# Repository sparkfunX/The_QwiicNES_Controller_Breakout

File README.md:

# The_QwiicNES_Controller_Breakout
Qwiic to Nintendo Entertainment System Controller Board

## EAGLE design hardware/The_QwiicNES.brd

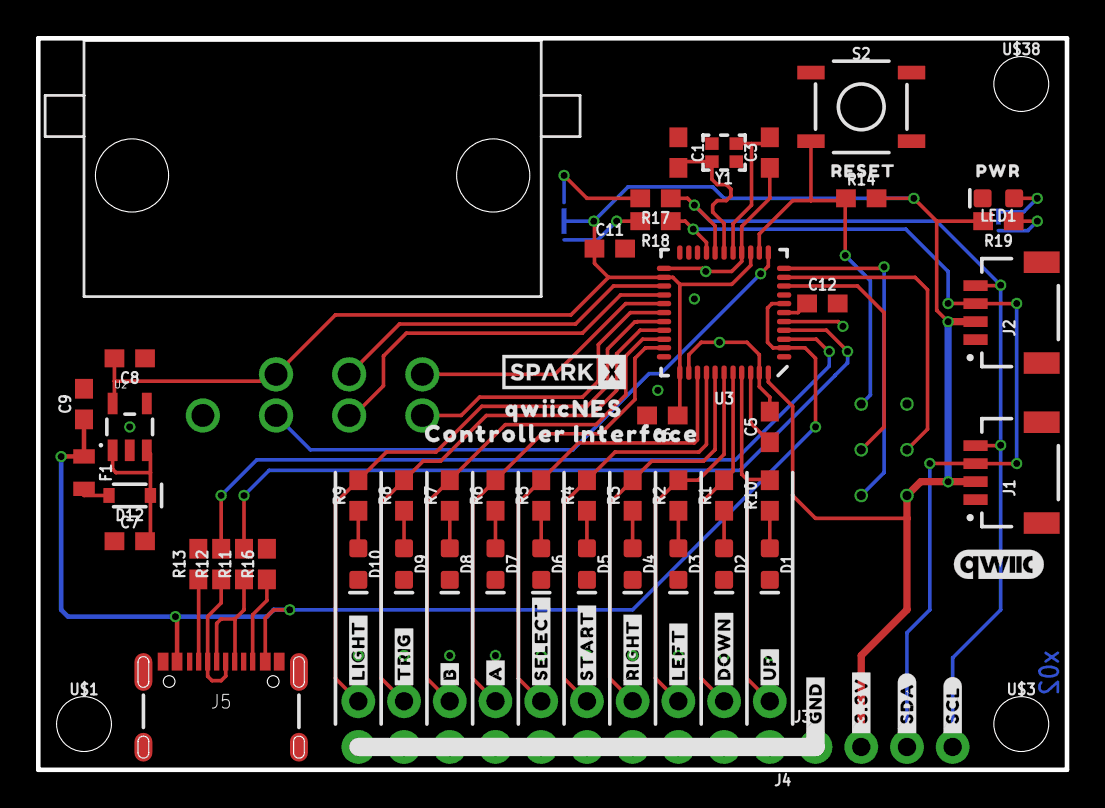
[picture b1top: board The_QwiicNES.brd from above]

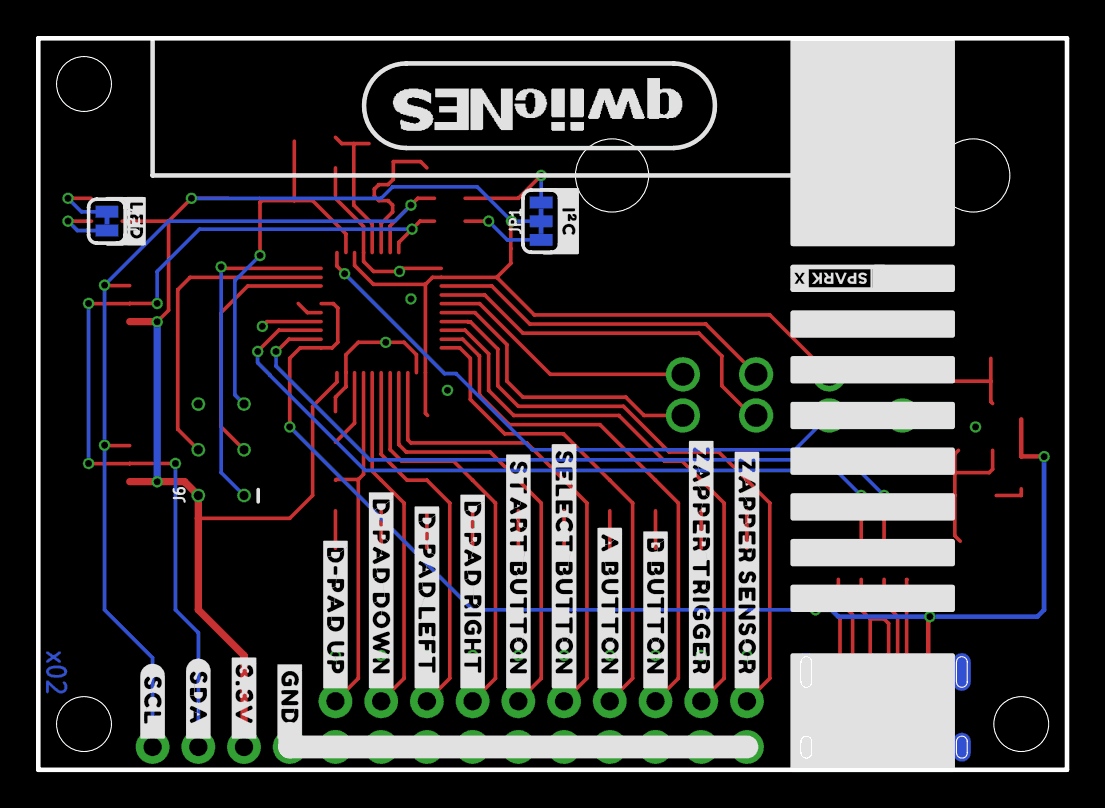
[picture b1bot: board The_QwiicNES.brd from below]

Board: 2 copper layers, 57.1 x 40.6 mm, 95 parts (21 on the bottom side), 50 nets.

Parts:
C1, C3: 22pF; 0603
C5, C6: 0.1uF; 0603
C7, C8: 10uF; 0603
C9, C11, C12: 1.0uF; 0603
D1, D2, D3, D4, D5, D6, D7, D8, D9, D10: GREEN; LED-0603
D12: 3A/10V/280mV; SOD-323
F1: 6V 0.5A; 0805
FRAME1: FRAME-LETTER; CREATIVE_COMMONS
J1, J2: QWIIC_RIGHT_ANGLE; JST04_1MM_RA
J3: 1X04_NO_SILK
J4: 2X10_NOSILK
J5: USB-C-16P-5
J6: AVR_SPI_PROG_3X2TESTPOINTS; 2X3_TEST_POINTS
J7: NES_CONTROLLER_PORT; NES_CONTROLLER_PORT_7PIN_90
JP1: JUMPER-SMT_3_2-NC_TRACE_SILK; SMT-JUMPER_3_2-NC_TRACE_SILK
JP2: JUMPER-SMT_2_NC_TRACE_SILK; SMT-JUMPER_2_NC_TRACE_SILK
LED1: RED; LED-0603
R1, R2, R3, R4, R5, R6, R7, R8, R9, R10, R19: 1k; 0603
R11, R12: 22; 0603
R13, R16: 5.1k; 0603
R14: 10k; 0603
R17, R18: 2.2k; 0603
S2: MOMENTARY-SWITCH-SPST-SMD-5.2MM-TALL; TACTILE_SWITCH_SMD_5.2MM
U2: 3.3V; SOT23-5
U3: 32U4; QFN-44-NOPAD_1:1-LESS_PASTE
U$1, U$3, U$38: STAND-OFF-TIGHT
U$2: SPARKX-SMALL
U$4: #LIGHT#0
U$5: #TRIG#0
U$6: #B#0
U$7: #A#0
U$8: #SELECT#0
U$9: #START#0
U$10: #RIGHT#0
U$11: #LEFT#0
U$12: #DOWN#0
U$13: #UP#0
U$14: #_GND#0
U$15: #_SDA#0
U$16: #_SCL#0
U$17: #_3#3V#0
U$18: PWR0
U$19: RESET0
U$20: SPARKX-TINY
U$21: #ZAPPER_SENSOR_#0
U$22: #ZAPPER_TRIGGER_#0
U$23: #B_BUTTON_#0
U$24: #A_BUTTON_#0
U$25: #SELECT_BUTTON_#0
U$26: #START_BUTTON_#0
U$27: #D#PAD_RIGHT_#0
U$28: #D#PAD_LEFT_#0
U$29: #D#PAD_DOWN_#0
U$30: #D#PAD_UP_#0
U$31: #GND_#0
U$32: #SDA_#0
U$33: #SCL_#0
U$34: #3#3V_#0
U$35: #I�C#0
U$36: #LED#0
U$37: QWIICNESS#PNG
U$39: QWIICNES0
U$40: CONTROLLER_INTERFACE0
U$41: QWIIC_5MM
Y1: 16MHz; CRYSTAL-SMD-2.0X1.6MM

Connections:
3.3V: C6.1, C8.2, C11.1, J1.2, J2.2, J3.2, J6.2, J7.7, JP1.2, R14.2, R19.2, U2.5, U3.14, U3.24, U3.34, U3.44
5V: C7.2, D12.C, U2.1, U2.3
!RESET: J6.5, R14.1, S2.3, U3.13
AREF: C5.1, U3.42
A_LED: J4.13, R6.2, U3.32
B_LED: J4.15, R7.2, U3.31
D-_HV: J5.A7, J5.B7, R12.1
DI: J6.1, U3.11
DN_LED: J4.3, R1.2, U3.40
DO: J6.4, U3.10
DP_HV: J5.A6, J5.B6, R11.1
D_N: R12.2, U3.3
D_P: R11.2, U3.4
GND: C1.1, C3.1, C5.2, C6.2, C7.1, C8.1, C9.2, C11.2, C12.2, D1.C, D2.C, D3.C, D4.C, D5.C, D6.C, D7.C, D8.C, D9.C, D10.C, J1.1, J2.1, J3.1, J4.2, J4.4, J4.6, J4.8, J4.10, J4.12, J4.14, J4.16, J4.18, J4.20, J5.GND, J5.GND2, J6.6, J7.1, LED1.C, R13.2, R16.2, S2.1, U2.2, U3.5, U3.15, U3.23, U3.33, U3.35, U3.43
LF_LED: J4.5, R2.2, U3.39
unnamed: C3.2, U3.16, Y1.1
unnamed: C1.2, U3.17, Y1.3
unnamed: D1.A, R10.1
unnamed: D2.A, R1.1
unnamed: D3.A, R2.1
unnamed: D4.A, R3.1
unnamed: D5.A, R4.1
unnamed: D6.A, R5.1
unnamed: J5.A5, R13.1
unnamed: J5.B5, R16.1
unnamed: D8.A, R7.1
unnamed: D7.A, R6.1
unnamed: JP2.2, R19.1
unnamed: JP2.1, LED1.A
unnamed: JP1.3, R17.2
unnamed: JP1.1, R18.2
unnamed: D10.A, R9.1
unnamed: D9.A, R8.1
NES_CLK: J7.2, U3.12
NES_DATA: J7.4, U3.28
NES_LATCH: J7.3, U3.26
RT_LED: J4.7, R3.2, U3.38
SCK: J6.3, U3.9
SCL: J1.4, J2.4, J3.4, R17.1, U3.18
SDA: J1.3, J2.3, J3.3, R18.1, U3.19
SELECT_LED: J4.11, R5.2, U3.36
START_LED: J4.9, R4.2, U3.37
UCAP: C12.1, U3.6
UP_LED: J4.1, R10.2, U3.41
USB_RAW: D12.A, F1.2
V_USB: C9.1, F1.1, J5.VBUS1, J5.VBUS2, U3.2, U3.7
ZAP_LIGHT: J7.6, U3.25
ZAP_LIGHT_LED: J4.19, R9.2, U3.29
ZAP_TRIGGER: J7.5, U3.27
ZAP_TRIG_LED: J4.17, R8.2, U3.30

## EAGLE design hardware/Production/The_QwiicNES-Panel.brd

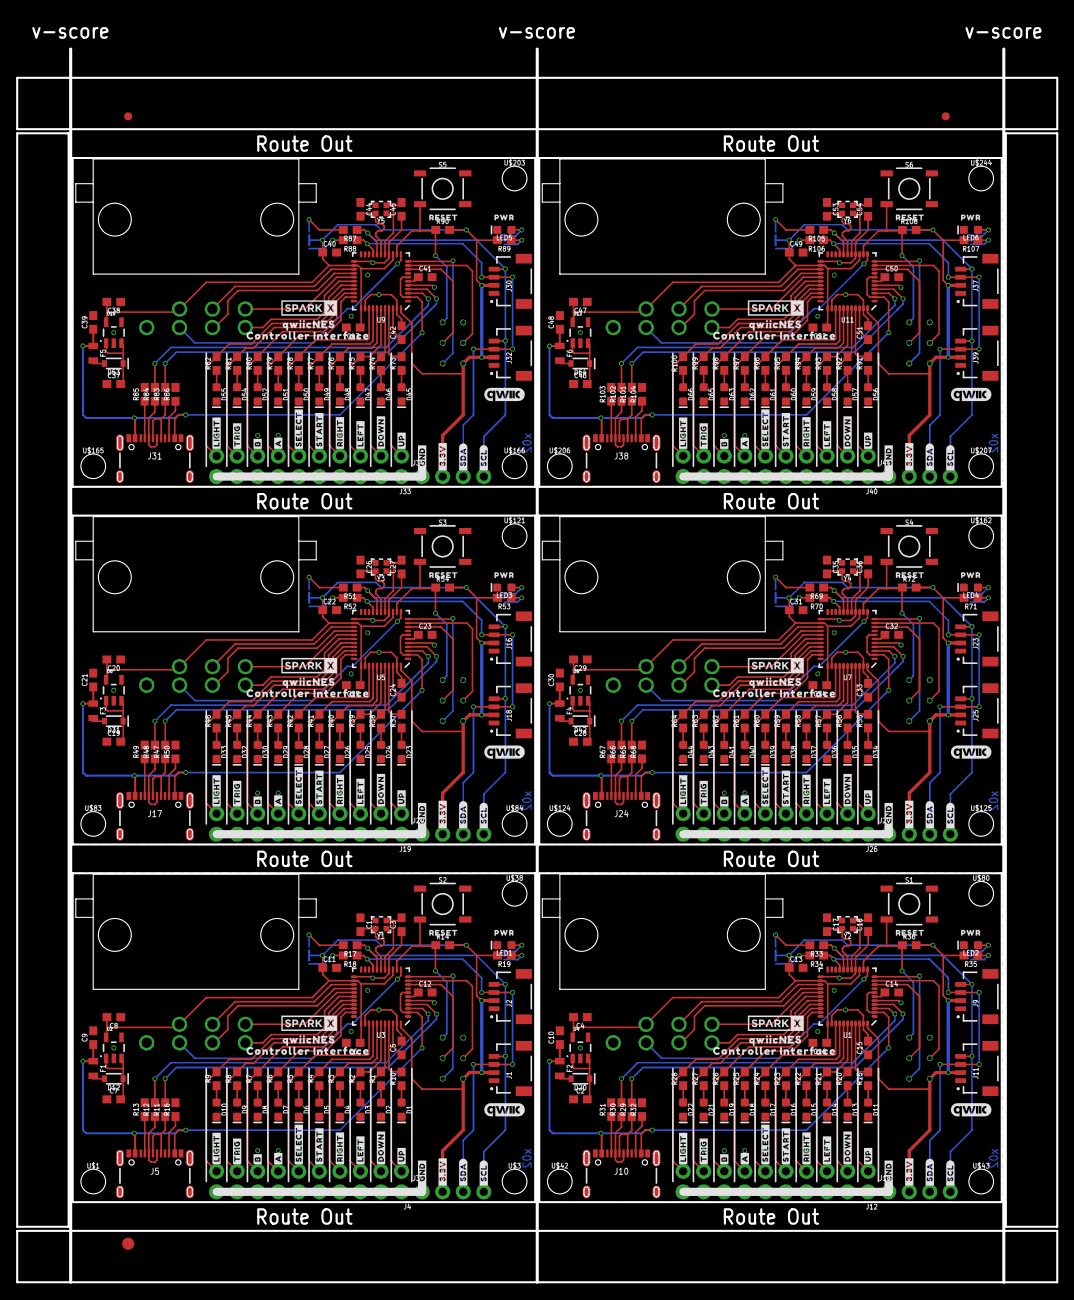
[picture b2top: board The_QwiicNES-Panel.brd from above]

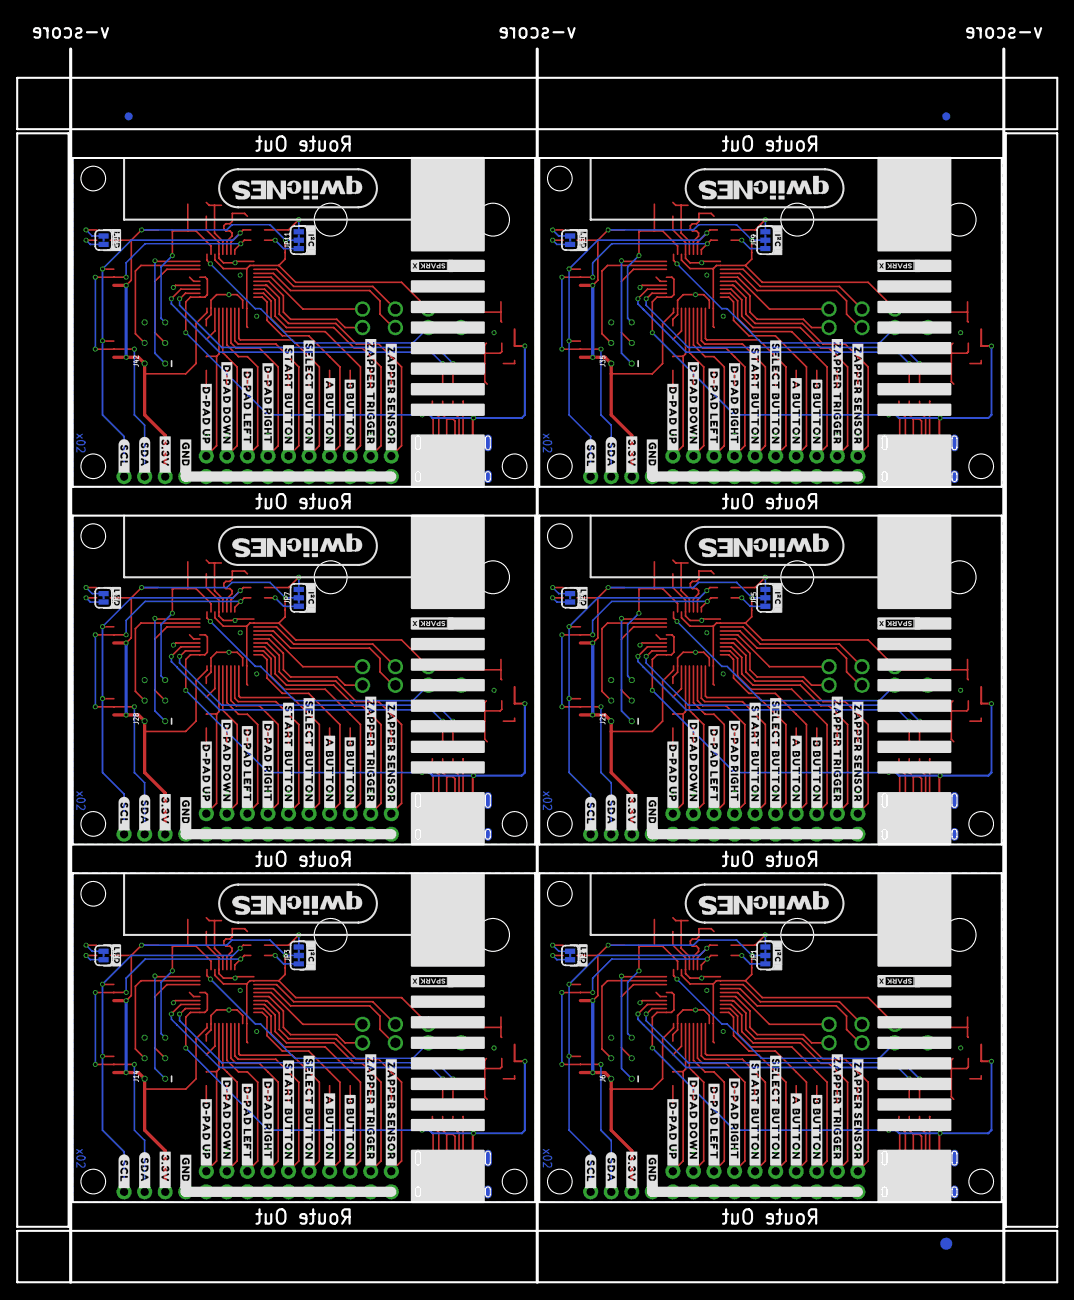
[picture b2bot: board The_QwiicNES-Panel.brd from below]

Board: 2 copper layers, 128.4 x 156.3 mm, 570 parts (129 on the bottom side), 300 nets.

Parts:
C1, C3, C17, C18, C26, C27, C35, C36, C44, C45, C53, C54: 22pF; 0603
C2, C4, C7, C8, C19, C20, C28, C29, C37, C38, C46, C47: 10uF; 0603
C5, C6, C15, C16, C24, C25, C33, C34, C42, C43, C51, C52: 0.1uF; 0603
C9, C10, C11, C12, C13, C14, C21, C22, C23, C30, C31, C32, C39, C40, C41, C48, C49, C50: 1.0uF; 0603
D1, D2, D3, D4, D5, D6, D7, D8, D9, D10, D11, D13, D14, D15, D16, D17, D18, D19, D21, D22, D23, D24, D25, D26, D27, D28, D29, D30, D32, D33, D34, D35, D36, D37, D38, D39, D40, D41, D43, D44, D45, D46, D47, D48, D49, D50, D51, D52, D54, D55, D56, D57, D58, D59, D60, D61, D62, D63, D65, D66: GREEN; LED-0603
D12, D20, D31, D42, D53, D64: 3A/10V/280mV; SOD-323
E$1, E$2, E$3, E$4: FIDUCIAL-1X2
E$5, E$6: FIDUCIAL-1.5X3
F1, F2, F3, F4, F5, F6: 6V 0.5A; 0805
J1, J2, J9, J11, J16, J18, J23, J25, J30, J32, J37, J39: QWIIC_RIGHT_ANGLE; JST04_1MM_RA
J3, J13, J20, J27, J34, J41: 1X04_NO_SILK
J4, J12, J19, J26, J33, J40: 2X10_NOSILK
J5, J10, J17, J24, J31, J38: USB-C-16P-5
J6, J14, J21, J28, J35, J42: AVR_SPI_PROG_3X2TESTPOINTS; 2X3_TEST_POINTS
J7, J8, J15, J22, J29, J36: NES_CONTROLLER_PORT; NES_CONTROLLER_PORT_7PIN_90
JP1, JP3, JP5, JP7, JP9, JP11: JUMPER-SMT_3_2-NC_TRACE_SILK; SMT-JUMPER_3_2-NC_TRACE_SILK
JP2, JP4, JP6, JP8, JP10, JP12: JUMPER-SMT_2_NC_TRACE_SILK; SMT-JUMPER_2_NC_TRACE_SILK
LED1, LED2, LED3, LED4, LED5, LED6: RED; LED-0603
R1, R2, R3, R4, R5, R6, R7, R8, R9, R10, R15, R19, R20, R21, R22, R23, R24, R25, R26, R27, R28, R35, R37, R38, R39, R40, R41, R42, R43, R44, R45, R46, R53, R55, R56, R57, R58, R59, R60, R61, R62, R63, R64, R71, R73, R74, R75, R76, R77, R78, R79, R80, R81, R82, R89, R91, R92, R93, R94, R95, R96, R97, R98, R99, R100, R107: 1k; 0603
R11, R12, R29, R30, R47, R48, R65, R66, R83, R84, R101, R102: 22; 0603
R13, R16, R31, R32, R49, R50, R67, R68, R85, R86, R103, R104: 5.1k; 0603
R14, R36, R54, R72, R90, R108: 10k; 0603
R17, R18, R33, R34, R51, R52, R69, R70, R87, R88, R105, R106: 2.2k; 0603
S1, S2, S3, S4, S5, S6: MOMENTARY-SWITCH-SPST-SMD-5.2MM-TALL; TACTILE_SWITCH_SMD_5.2MM
U1, U3, U5, U7, U9, U11: 32U4; QFN-44-NOPAD_1:1-LESS_PASTE
U2, U4, U6, U8, U10, U12: 3.3V; SOT23-5
U$1, U$3, U$38, U$42, U$43, U$80, U$83, U$84, U$121, U$124, U$125, U$162, U$165, U$166, U$203, U$206, U$207, U$244: STAND-OFF-TIGHT
U$2, U$79, U$120, U$161, U$202, U$243: SPARKX-SMALL
U$4, U$44, U$85, U$126, U$167, U$208: #LIGHT#0
U$5, U$45, U$86, U$127, U$168, U$209: #TRIG#0
U$6, U$46, U$87, U$128, U$169, U$210: #B#0
U$7, U$47, U$88, U$129, U$170, U$211: #A#0
U$8, U$48, U$89, U$130, U$171, U$212: #SELECT#0
U$9, U$49, U$90, U$131, U$172, U$213: #START#0
U$10, U$50, U$91, U$132, U$173, U$214: #RIGHT#0
U$11, U$51, U$92, U$133, U$174, U$215: #LEFT#0
U$12, U$52, U$93, U$134, U$175, U$216: #DOWN#0
U$13, U$53, U$94, U$135, U$176, U$217: #UP#0
U$14, U$59, U$100, U$141, U$182, U$223: #_GND#0
U$15, U$54, U$95, U$136, U$177, U$218: #_SDA#0
U$16, U$55, U$96, U$137, U$178, U$219: #_SCL#0
U$17, U$56, U$97, U$138, U$179, U$220: #_3#3V#0
U$18, U$57, U$98, U$139, U$180, U$221: PWR0
U$19, U$58, U$99, U$140, U$181, U$222: RESET0
U$20, U$75, U$116, U$157, U$198, U$239: SPARKX-TINY
U$21, U$60, U$101, U$142, U$183, U$224: #ZAPPER_SENSOR_#0
U$22, U$61, U$102, U$143, U$184, U$225: #ZAPPER_TRIGGER_#0
U$23, U$62, U$103, U$144, U$185, U$226: #B_BUTTON_#0
U$24, U$63, U$104, U$145, U$186, U$227: #A_BUTTON_#0
U$25, U$64, U$105, U$146, U$187, U$228: #SELECT_BUTTON_#0
U$26, U$65, U$106, U$147, U$188, U$229: #START_BUTTON_#0
U$27, U$66, U$107, U$148, U$189, U$230: #D#PAD_RIGHT_#0
U$28, U$67, U$108, U$149, U$190, U$231: #D#PAD_LEFT_#0
U$29, U$68, U$109, U$150, U$191, U$232: #D#PAD_DOWN_#0
U$30, U$69, U$110, U$151, U$192, U$233: #D#PAD_UP_#0
U$31, U$70, U$111, U$152, U$193, U$234: #GND_#0
U$32, U$71, U$112, U$153, U$194, U$235: #SDA_#0
U$33, U$72, U$113, U$154, U$195, U$236: #SCL_#0
U$34, U$73, U$114, U$155, U$196, U$237: #3#3V_#0
U$35, U$74, U$115, U$156, U$197, U$238: #I�C#0
U$36, U$82, U$123, U$164, U$205, U$246: #LED#0
U$37, U$76, U$117, U$158, U$199, U$240: QWIICNESS#PNG
U$39, U$77, U$118, U$159, U$200, U$241: QWIICNES0
U$40, U$78, U$119, U$160, U$201, U$242: CONTROLLER_INTERFACE0
U$41, U$81, U$122, U$163, U$204, U$245: QWIIC_5MM
Y1, Y2, Y3, Y4, Y5, Y6: 16MHz; CRYSTAL-SMD-2.0X1.6MM

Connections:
3.3V: C6.1, C8.2, C11.1, J1.2, J2.2, J3.2, J6.2, J7.7, JP1.2, R14.2, R19.2, U2.5, U3.14, U3.24, U3.34, U3.44
3.3V1: C4.2, C13.1, C16.1, J8.7, J9.2, J11.2, J13.2, J14.2, JP3.2, R35.2, R36.2, U1.14, U1.24, U1.34, U1.44, U4.5
3.3V2: C20.2, C22.1, C25.1, J15.7, J16.2, J18.2, J20.2, J21.2, JP5.2, R53.2, R54.2, U5.14, U5.24, U5.34, U5.44, U6.5
3.3V3: C29.2, C31.1, C34.1, J22.7, J23.2, J25.2, J27.2, J28.2, JP7.2, R71.2, R72.2, U7.14, U7.24, U7.34, U7.44, U8.5
3.3V4: C38.2, C40.1, C43.1, J29.7, J30.2, J32.2, J34.2, J35.2, JP9.2, R89.2, R90.2, U9.14, U9.24, U9.34, U9.44, U10.5
3.3V5: C47.2, C49.1, C52.1, J36.7, J37.2, J39.2, J41.2, J42.2, JP11.2, R107.2, R108.2, U11.14, U11.24, U11.34, U11.44, U12.5
5V: C7.2, D12.C, U2.1, U2.3
5V1: C2.2, D20.C, U4.1, U4.3
5V2: C19.2, D31.C, U6.1, U6.3
5V3: C28.2, D42.C, U8.1, U8.3
5V4: C37.2, D53.C, U10.1, U10.3
5V5: C46.2, D64.C, U12.1, U12.3
!RESET: J6.5, R14.1, S2.3, U3.13
!RESET1: J14.5, R36.1, S1.3, U1.13
!RESET2: J21.5, R54.1, S3.3, U5.13
!RESET3: J28.5, R72.1, S4.3, U7.13
!RESET4: J35.5, R90.1, S5.3, U9.13
!RESET5: J42.5, R108.1, S6.3, U11.13
AREF: C5.1, U3.42
AREF1: C15.1, U1.42
AREF2: C24.1, U5.42
AREF3: C33.1, U7.42
AREF4: C42.1, U9.42
AREF5: C51.1, U11.42
A_LED: J4.13, R6.2, U3.32
A_LED1: J12.13, R25.2, U1.32
A_LED2: J19.13, R43.2, U5.32
A_LED3: J26.13, R61.2, U7.32
A_LED4: J33.13, R79.2, U9.32
A_LED5: J40.13, R97.2, U11.32
B_LED: J4.15, R7.2, U3.31
B_LED1: J12.15, R26.2, U1.31
B_LED2: J19.15, R44.2, U5.31
B_LED3: J26.15, R62.2, U7.31
B_LED4: J33.15, R80.2, U9.31
B_LED5: J40.15, R98.2, U11.31
D-_HV: J5.A7, J5.B7, R12.1
D-_HV1: J10.A7, J10.B7, R30.1
D-_HV2: J17.A7, J17.B7, R48.1
D-_HV3: J24.A7, J24.B7, R66.1
D-_HV4: J31.A7, J31.B7, R84.1
D-_HV5: J38.A7, J38.B7, R102.1
DI: J6.1, U3.11
DI1: J14.1, U1.11
DI2: J21.1, U5.11
DI3: J28.1, U7.11
DI4: J35.1, U9.11
DI5: J42.1, U11.11
DN_LED: J4.3, R1.2, U3.40
DN_LED1: J12.3, R20.2, U1.40
DN_LED2: J19.3, R38.2, U5.40
DN_LED3: J26.3, R56.2, U7.40
DN_LED4: J33.3, R74.2, U9.40
DN_LED5: J40.3, R92.2, U11.40
DO: J6.4, U3.10
DO1: J14.4, U1.10
DO2: J21.4, U5.10
DO3: J28.4, U7.10
DO4: J35.4, U9.10
DO5: J42.4, U11.10
DP_HV: J5.A6, J5.B6, R11.1
DP_HV1: J10.A6, J10.B6, R29.1
DP_HV2: J17.A6, J17.B6, R47.1
DP_HV3: J24.A6, J24.B6, R65.1
DP_HV4: J31.A6, J31.B6, R83.1
DP_HV5: J38.A6, J38.B6, R101.1
D_N: R12.2, U3.3
D_N1: R30.2, U1.3
D_N2: R48.2, U5.3
D_N3: R66.2, U7.3
D_N4: R84.2, U9.3
D_N5: R102.2, U11.3
D_P: R11.2, U3.4
D_P1: R29.2, U1.4
D_P2: R47.2, U5.4
D_P3: R65.2, U7.4
D_P4: R83.2, U9.4
D_P5: R101.2, U11.4
GND: C1.1, C3.1, C5.2, C6.2, C7.1, C8.1, C9.2, C11.2, C12.2, D1.C, D2.C, D3.C, D4.C, D5.C, D6.C, D7.C, D8.C, D9.C, D10.C, J1.1, J2.1, J3.1, J4.2, J4.4, J4.6, J4.8, J4.10, J4.12, J4.14, J4.16, J4.18, J4.20, J5.GND, J5.GND2, J6.6, J7.1, LED1.C, R13.2, R16.2, S2.1, U2.2, U3.5, U3.15, U3.23, U3.33, U3.35, U3.43
GND1: C2.1, C4.1, C10.2, C13.2, C14.2, C15.2, C16.2, C17.1, C18.1, D11.C, D13.C, D14.C, D15.C, D16.C, D17.C, D18.C, D19.C, D21.C, D22.C, J8.1, J9.1, J10.GND, J10.GND2, J11.1, J12.2, J12.4, J12.6, J12.8, J12.10, J12.12, J12.14, J12.16, J12.18, J12.20, J13.1, J14.6, LED2.C, R31.2, R32.2, S1.1, U1.5, U1.15, U1.23, U1.33, U1.35, U1.43, U4.2
GND2: C19.1, C20.1, C21.2, C22.2, C23.2, C24.2, C25.2, C26.1, C27.1, D23.C, D24.C, D25.C, D26.C, D27.C, D28.C, D29.C, D30.C, D32.C, D33.C, J15.1, J16.1, J17.GND, J17.GND2, J18.1, J19.2, J19.4, J19.6, J19.8, J19.10, J19.12, J19.14, J19.16, J19.18, J19.20, J20.1, J21.6, LED3.C, R49.2, R50.2, S3.1, U5.5, U5.15, U5.23, U5.33, U5.35, U5.43, U6.2
GND3: C28.1, C29.1, C30.2, C31.2, C32.2, C33.2, C34.2, C35.1, C36.1, D34.C, D35.C, D36.C, D37.C, D38.C, D39.C, D40.C, D41.C, D43.C, D44.C, J22.1, J23.1, J24.GND, J24.GND2, J25.1, J26.2, J26.4, J26.6, J26.8, J26.10, J26.12, J26.14, J26.16, J26.18, J26.20, J27.1, J28.6, LED4.C, R67.2, R68.2, S4.1, U7.5, U7.15, U7.23, U7.33, U7.35, U7.43, U8.2
GND4: C37.1, C38.1, C39.2, C40.2, C41.2, C42.2, C43.2, C44.1, C45.1, D45.C, D46.C, D47.C, D48.C, D49.C, D50.C, D51.C, D52.C, D54.C, D55.C, J29.1, J30.1, J31.GND, J31.GND2, J32.1, J33.2, J33.4, J33.6, J33.8, J33.10, J33.12, J33.14, J33.16, J33.18, J33.20, J34.1, J35.6, LED5.C, R85.2, R86.2, S5.1, U9.5, U9.15, U9.23, U9.33, U9.35, U9.43, U10.2
GND5: C46.1, C47.1, C48.2, C49.2, C50.2, C51.2, C52.2, C53.1, C54.1, D56.C, D57.C, D58.C, D59.C, D60.C, D61.C, D62.C, D63.C, D65.C, D66.C, J36.1, J37.1, J38.GND, J38.GND2, J39.1, J40.2, J40.4, J40.6, J40.8, J40.10, J40.12, J40.14, J40.16, J40.18, J40.20, J41.1, J42.6, LED6.C, R103.2, R104.2, S6.1, U11.5, U11.15, U11.23, U11.33, U11.35, U11.43, U12.2
LF_LED: J4.5, R2.2, U3.39
LF_LED1: J12.5, R21.2, U1.39
LF_LED2: J19.5, R39.2, U5.39
LF_LED3: J26.5, R57.2, U7.39
LF_LED4: J33.5, R75.2, U9.39
LF_LED5: J40.5, R93.2, U11.39
unnamed: C3.2, U3.16, Y1.1
unnamed: C1.2, U3.17, Y1.3
unnamed: D1.A, R10.1
unnamed: D2.A, R1.1
unnamed: D3.A, R2.1
unnamed: D4.A, R3.1
unnamed: D5.A, R4.1
unnamed: D6.A, R5.1
unnamed: J5.A5, R13.1
unnamed: J5.B5, R16.1
unnamed: D8.A, R7.1
unnamed: D7.A, R6.1
unnamed: JP2.2, R19.1
unnamed: JP2.1, LED1.A
unnamed: C18.2, U1.16, Y2.1
unnamed: C17.2, U1.17, Y2.3
unnamed: J10.A5, R31.1
unnamed: J10.B5, R32.1
unnamed: D11.A, R15.1
unnamed: D13.A, R20.1
unnamed: JP1.3, R17.2
unnamed: JP1.1, R18.2
unnamed: D10.A, R9.1
unnamed: D9.A, R8.1
unnamed: D14.A, R21.1
unnamed: D15.A, R22.1
unnamed: D16.A, R23.1
unnamed: D17.A, R24.1
unnamed: D19.A, R26.1
unnamed: D18.A, R25.1
unnamed: JP3.3, R33.2
unnamed: JP3.1, R34.2
unnamed: D22.A, R28.1
unnamed: D21.A, R27.1
unnamed: JP4.2, R35.1
unnamed: JP4.1, LED2.A
unnamed: C27.2, U5.16, Y3.1
unnamed: C26.2, U5.17, Y3.3
unnamed: J17.A5, R49.1
unnamed: J17.B5, R50.1
unnamed: D23.A, R37.1
unnamed: D24.A, R38.1
unnamed: D25.A, R39.1
unnamed: D26.A, R40.1
unnamed: D27.A, R41.1
unnamed: D28.A, R42.1
unnamed: D30.A, R44.1
unnamed: D29.A, R43.1
unnamed: JP5.3, R51.2
unnamed: JP5.1, R52.2
unnamed: D33.A, R46.1
unnamed: D32.A, R45.1
unnamed: JP6.2, R53.1
unnamed: JP6.1, LED3.A
unnamed: C36.2, U7.16, Y4.1
unnamed: C35.2, U7.17, Y4.3
unnamed: J24.A5, R67.1
unnamed: J24.B5, R68.1
unnamed: D34.A, R55.1
unnamed: D35.A, R56.1
unnamed: D36.A, R57.1
unnamed: D37.A, R58.1
unnamed: D38.A, R59.1
unnamed: D39.A, R60.1
unnamed: D41.A, R62.1
unnamed: D40.A, R61.1
unnamed: JP7.3, R69.2
unnamed: JP7.1, R70.2
unnamed: D44.A, R64.1
unnamed: D43.A, R63.1
unnamed: JP8.2, R71.1
unnamed: JP8.1, LED4.A
unnamed: C45.2, U9.16, Y5.1
unnamed: C44.2, U9.17, Y5.3
unnamed: J31.A5, R85.1
unnamed: J31.B5, R86.1
unnamed: D45.A, R73.1
unnamed: D46.A, R74.1
unnamed: D47.A, R75.1
unnamed: D48.A, R76.1
unnamed: D49.A, R77.1
unnamed: D50.A, R78.1
unnamed: D52.A, R80.1
unnamed: D51.A, R79.1
unnamed: JP9.3, R87.2
unnamed: JP9.1, R88.2
unnamed: D55.A, R82.1
unnamed: D54.A, R81.1
unnamed: JP10.2, R89.1
unnamed: JP10.1, LED5.A
unnamed: C54.2, U11.16, Y6.1
unnamed: C53.2, U11.17, Y6.3
unnamed: J38.A5, R103.1
unnamed: J38.B5, R104.1
unnamed: D56.A, R91.1
unnamed: D57.A, R92.1
unnamed: D58.A, R93.1
unnamed: D59.A, R94.1
unnamed: D60.A, R95.1
unnamed: D61.A, R96.1
unnamed: D63.A, R98.1
unnamed: D62.A, R97.1
unnamed: JP11.3, R105.2
unnamed: JP11.1, R106.2
unnamed: D66.A, R100.1
unnamed: D65.A, R99.1
unnamed: JP12.2, R107.1
unnamed: JP12.1, LED6.A
NES_CLK: J7.2, U3.12
NES_CLK1: J8.2, U1.12
NES_CLK2: J15.2, U5.12
NES_CLK3: J22.2, U7.12
NES_CLK4: J29.2, U9.12
NES_CLK5: J36.2, U11.12
NES_DATA: J7.4, U3.28
NES_DATA1: J8.4, U1.28
NES_DATA2: J15.4, U5.28
NES_DATA3: J22.4, U7.28
NES_DATA4: J29.4, U9.28
NES_DATA5: J36.4, U11.28
NES_LATCH: J7.3, U3.26
NES_LATCH1: J8.3, U1.26
NES_LATCH2: J15.3, U5.26
NES_LATCH3: J22.3, U7.26
NES_LATCH4: J29.3, U9.26
NES_LATCH5: J36.3, U11.26
RT_LED: J4.7, R3.2, U3.38
RT_LED1: J12.7, R22.2, U1.38
RT_LED2: J19.7, R40.2, U5.38
RT_LED3: J26.7, R58.2, U7.38
RT_LED4: J33.7, R76.2, U9.38
RT_LED5: J40.7, R94.2, U11.38
SCK: J6.3, U3.9
SCK1: J14.3, U1.9
SCK2: J21.3, U5.9
SCK3: J28.3, U7.9
SCK4: J35.3, U9.9
SCK5: J42.3, U11.9
SCL: J1.4, J2.4, J3.4, R17.1, U3.18
SCL1: J9.4, J11.4, J13.4, R33.1, U1.18
SCL2: J16.4, J18.4, J20.4, R51.1, U5.18
SCL3: J23.4, J25.4, J27.4, R69.1, U7.18
SCL4: J30.4, J32.4, J34.4, R87.1, U9.18
SCL5: J37.4, J39.4, J41.4, R105.1, U11.18
SDA: J1.3, J2.3, J3.3, R18.1, U3.19
SDA1: J9.3, J11.3, J13.3, R34.1, U1.19
SDA2: J16.3, J18.3, J20.3, R52.1, U5.19
SDA3: J23.3, J25.3, J27.3, R70.1, U7.19
SDA4: J30.3, J32.3, J34.3, R88.1, U9.19
SDA5: J37.3, J39.3, J41.3, R106.1, U11.19
SELECT_LED: J4.11, R5.2, U3.36
SELECT_LED1: J12.11, R24.2, U1.36
SELECT_LED2: J19.11, R42.2, U5.36
SELECT_LED3: J26.11, R60.2, U7.36
SELECT_LED4: J33.11, R78.2, U9.36
SELECT_LED5: J40.11, R96.2, U11.36
START_LED: J4.9, R4.2, U3.37
START_LED1: J12.9, R23.2, U1.37
START_LED2: J19.9, R41.2, U5.37
START_LED3: J26.9, R59.2, U7.37
START_LED4: J33.9, R77.2, U9.37
START_LED5: J40.9, R95.2, U11.37
UCAP: C12.1, U3.6
UCAP1: C14.1, U1.6
UCAP2: C23.1, U5.6
UCAP3: C32.1, U7.6
UCAP4: C41.1, U9.6
UCAP5: C50.1, U11.6
UP_LED: J4.1, R10.2, U3.41
UP_LED1: J12.1, R15.2, U1.41
UP_LED2: J19.1, R37.2, U5.41
UP_LED3: J26.1, R55.2, U7.41
UP_LED4: J33.1, R73.2, U9.41
UP_LED5: J40.1, R91.2, U11.41
USB_RAW: D12.A, F1.2
USB_RAW1: D20.A, F2.2
USB_RAW2: D31.A, F3.2
USB_RAW3: D42.A, F4.2
USB_RAW4: D53.A, F5.2
USB_RAW5: D64.A, F6.2
V_USB: C9.1, F1.1, J5.VBUS1, J5.VBUS2, U3.2, U3.7
V_USB1: C10.1, F2.1, J10.VBUS1, J10.VBUS2, U1.2, U1.7
V_USB2: C21.1, F3.1, J17.VBUS1, J17.VBUS2, U5.2, U5.7
V_USB3: C30.1, F4.1, J24.VBUS1, J24.VBUS2, U7.2, U7.7
V_USB4: C39.1, F5.1, J31.VBUS1, J31.VBUS2, U9.2, U9.7
V_USB5: C48.1, F6.1, J38.VBUS1, J38.VBUS2, U11.2, U11.7
ZAP_LIGHT: J7.6, U3.25
ZAP_LIGHT1: J8.6, U1.25
ZAP_LIGHT2: J15.6, U5.25
ZAP_LIGHT3: J22.6, U7.25
ZAP_LIGHT4: J29.6, U9.25
ZAP_LIGHT5: J36.6, U11.25
ZAP_LIGHT_LED: J4.19, R9.2, U3.29
ZAP_LIGHT_LED1: J12.19, R28.2, U1.29
ZAP_LIGHT_LED2: J19.19, R46.2, U5.29
ZAP_LIGHT_LED3: J26.19, R64.2, U7.29
ZAP_LIGHT_LED4: J33.19, R82.2, U9.29
ZAP_LIGHT_LED5: J40.19, R100.2, U11.29
ZAP_TRIGGER: J7.5, U3.27
ZAP_TRIGGER1: J8.5, U1.27
ZAP_TRIGGER2: J15.5, U5.27
ZAP_TRIGGER3: J22.5, U7.27
ZAP_TRIGGER4: J29.5, U9.27
ZAP_TRIGGER5: J36.5, U11.27
ZAP_TRIG_LED: J4.17, R8.2, U3.30
ZAP_TRIG_LED1: J12.17, R27.2, U1.30
ZAP_TRIG_LED2: J19.17, R45.2, U5.30
ZAP_TRIG_LED3: J26.17, R63.2, U7.30
ZAP_TRIG_LED4: J33.17, R81.2, U9.30
ZAP_TRIG_LED5: J40.17, R99.2, U11.30

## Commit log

2021-01-04 x01 review
2021-01-10 x01 initial order
2021-03-03 x02
    Change NES controller port post size from 0.13 to 0.16
2021-03-03 update library part
2021-03-15 Create QwiicNES_Firmware-v01.ino
    Adding firmware file
2021-03-16 reduced paste on main IC
2021-05-19 Add programming batch file

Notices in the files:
parts and their libraries:
SparkFun-IC-Microcontroller: Licensing: Creative Commons ShareAlike 4.0 International - https://creativecommons.org/licenses/by-sa/4.0
SparkFun-Aesthetics: Released under the Creative Commons Attribution Share-Alike 4.0 License
SparkFun-Aesthetics: https://creativecommons.org/licenses/by-sa/4.0
